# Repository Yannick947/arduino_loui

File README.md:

This repo can be used to play looping louie in different modes. Photocells are used to detect the chip count for each player. Automatic speech output is implemented and the game is stopped automatically when a player lost.

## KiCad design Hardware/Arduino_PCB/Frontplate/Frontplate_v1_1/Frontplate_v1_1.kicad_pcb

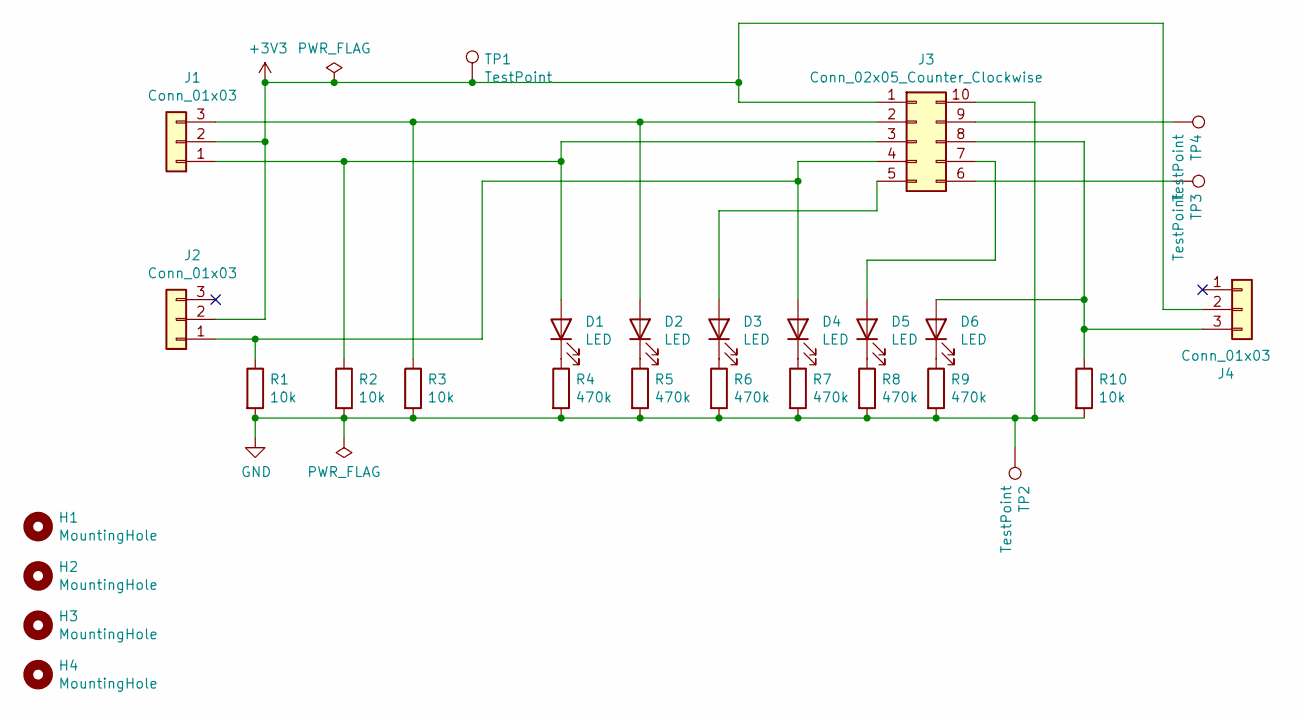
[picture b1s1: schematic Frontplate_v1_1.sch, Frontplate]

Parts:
D1, D2, D3, D4, D5, D6: LED; LED_D5.0mm
H1, H2, H3, H4: MountingHole; MountingHole_3.2mm_M3_DIN965_Pad
J1, J2, J4: Conn_01x03; PinHeader_1x03_P2.54mm_Vertical
J3: Conn_02x05_Counter_Clockwise; Muekra_10pol_Pfostenstecker
R1, R2, R3, R10: 10k; R_Axial_DIN0207_L6.3mm_D2.5mm_P10.16mm_Horizontal
R4, R5, R6, R7, R8, R9: 470k; R_Axial_DIN0207_L6.3mm_D2.5mm_P10.16mm_Horizontal
TP1, TP3, TP4: TestPoint; TestPoint_Pad_D2.0mm
TP2: TestPoint; TestPoint_Pad_2.0x2.0mm

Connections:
+3V3: J1.2, J2.2, J3.1, J4.2, TP1.1
GND: J3.10, R1.2, R2.2, R3.2, R4.2, R5.2, R6.2, R7.2, R8.2, R9.2, R10.2, TP2.1
unnamed: D1.1 (K), R4.1
unnamed: D1.2 (A), J1.1, J3.3, R2.1
unnamed: D2.1 (K), R5.1
unnamed: D2.2 (A), J1.3, J3.2, R3.1
unnamed: D3.1 (K), R6.1
unnamed: D3.2 (A), J3.5
unnamed: D4.1 (K), R7.1
unnamed: D4.2 (A), J2.1, J3.4, R1.1
unnamed: D5.1 (K), R8.1
unnamed: D5.2 (A), J3.7
unnamed: D6.1 (K), R9.1
unnamed: D6.2 (A), J3.8, J4.3, R10.1
unnamed: J3.6, TP3.1
unnamed: J3.9, TP4.1

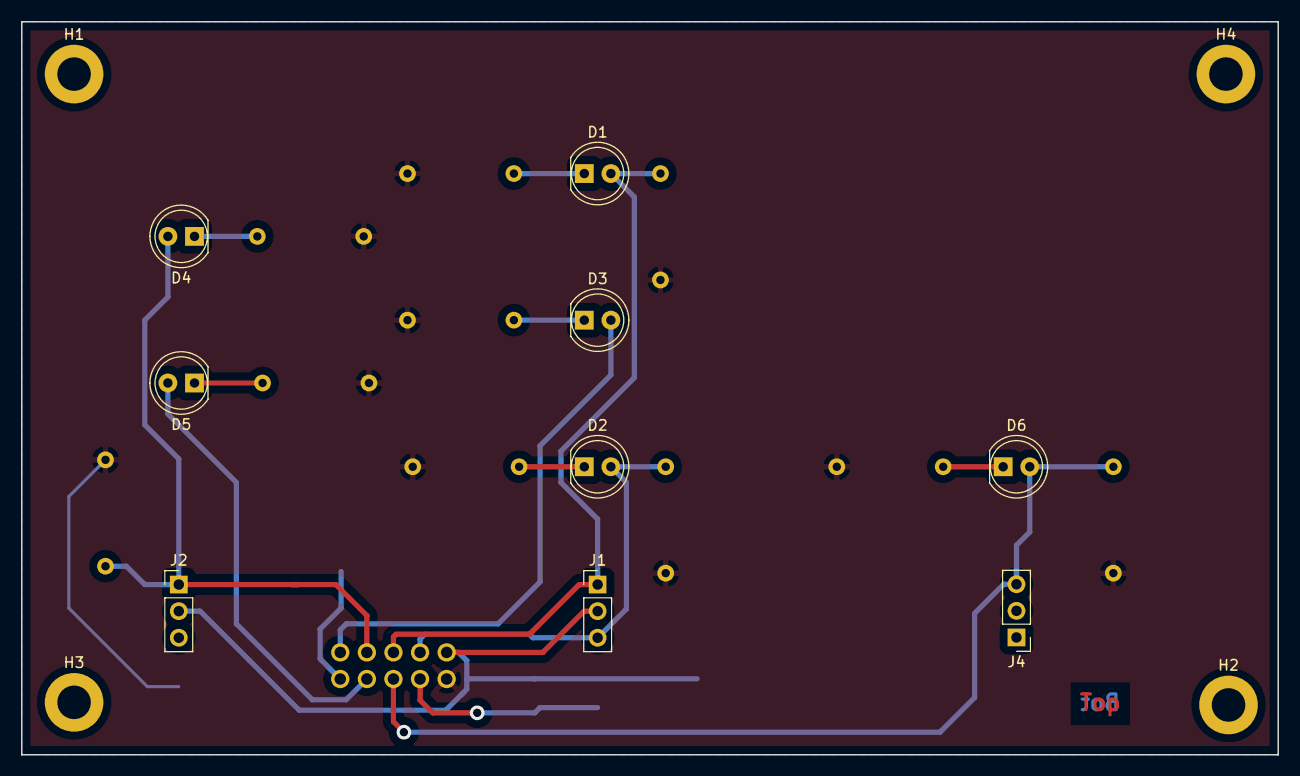
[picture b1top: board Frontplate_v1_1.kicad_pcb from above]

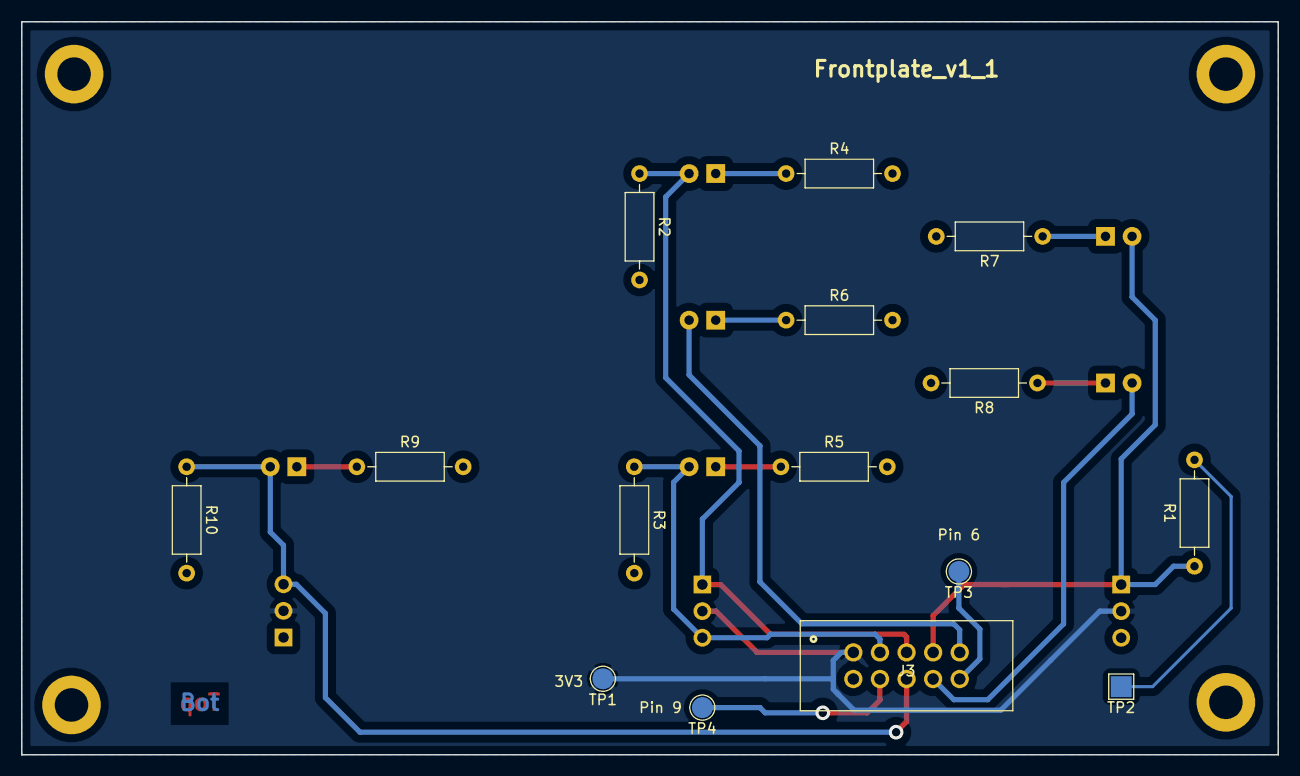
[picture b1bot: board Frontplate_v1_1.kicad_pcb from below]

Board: 2 copper layers, 120.0 x 70.0 mm, 28 parts (15 on the bottom side), 16 nets.

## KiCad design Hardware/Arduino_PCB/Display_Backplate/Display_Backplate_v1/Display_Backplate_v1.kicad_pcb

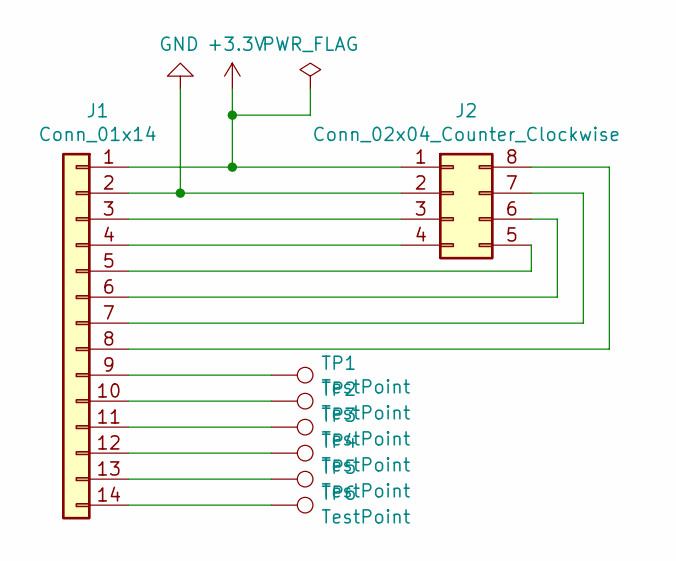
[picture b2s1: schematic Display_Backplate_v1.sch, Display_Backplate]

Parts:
J1: Conn_01x14; PinSocket_1x14_P2.54mm_Vertical
J2: Conn_02x04_Counter_Clockwise; Muekra_8pol_Pfostenstecker
TP1, TP2, TP3, TP4, TP5, TP6: TestPoint; TestPoint_Pad_D2.5mm

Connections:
+3V3: J1.1, J2.1
GND: J1.2, J2.2
unnamed: J1.3, J2.3
unnamed: J1.4, J2.4
unnamed: J1.5, J2.5
unnamed: J1.6, J2.6
unnamed: J1.7, J2.7
unnamed: J1.8, J2.8
unnamed: J1.9, TP1.1
unnamed: J1.10, TP2.1
unnamed: J1.11, TP3.1
unnamed: J1.12, TP4.1
unnamed: J1.13, TP5.1
unnamed: J1.14, TP6.1

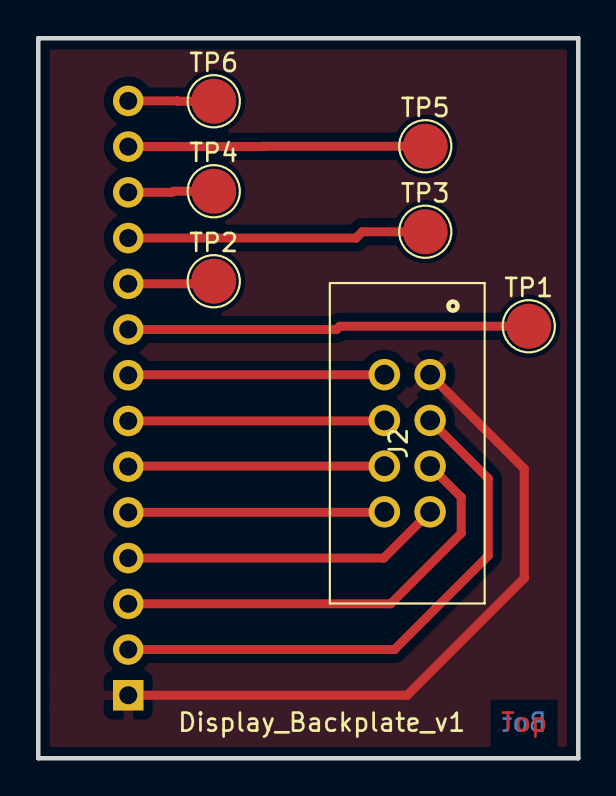
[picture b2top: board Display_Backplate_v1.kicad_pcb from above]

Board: 2 copper layers, 30.0 x 40.0 mm, 8 parts (1 on the bottom side), 14 nets.

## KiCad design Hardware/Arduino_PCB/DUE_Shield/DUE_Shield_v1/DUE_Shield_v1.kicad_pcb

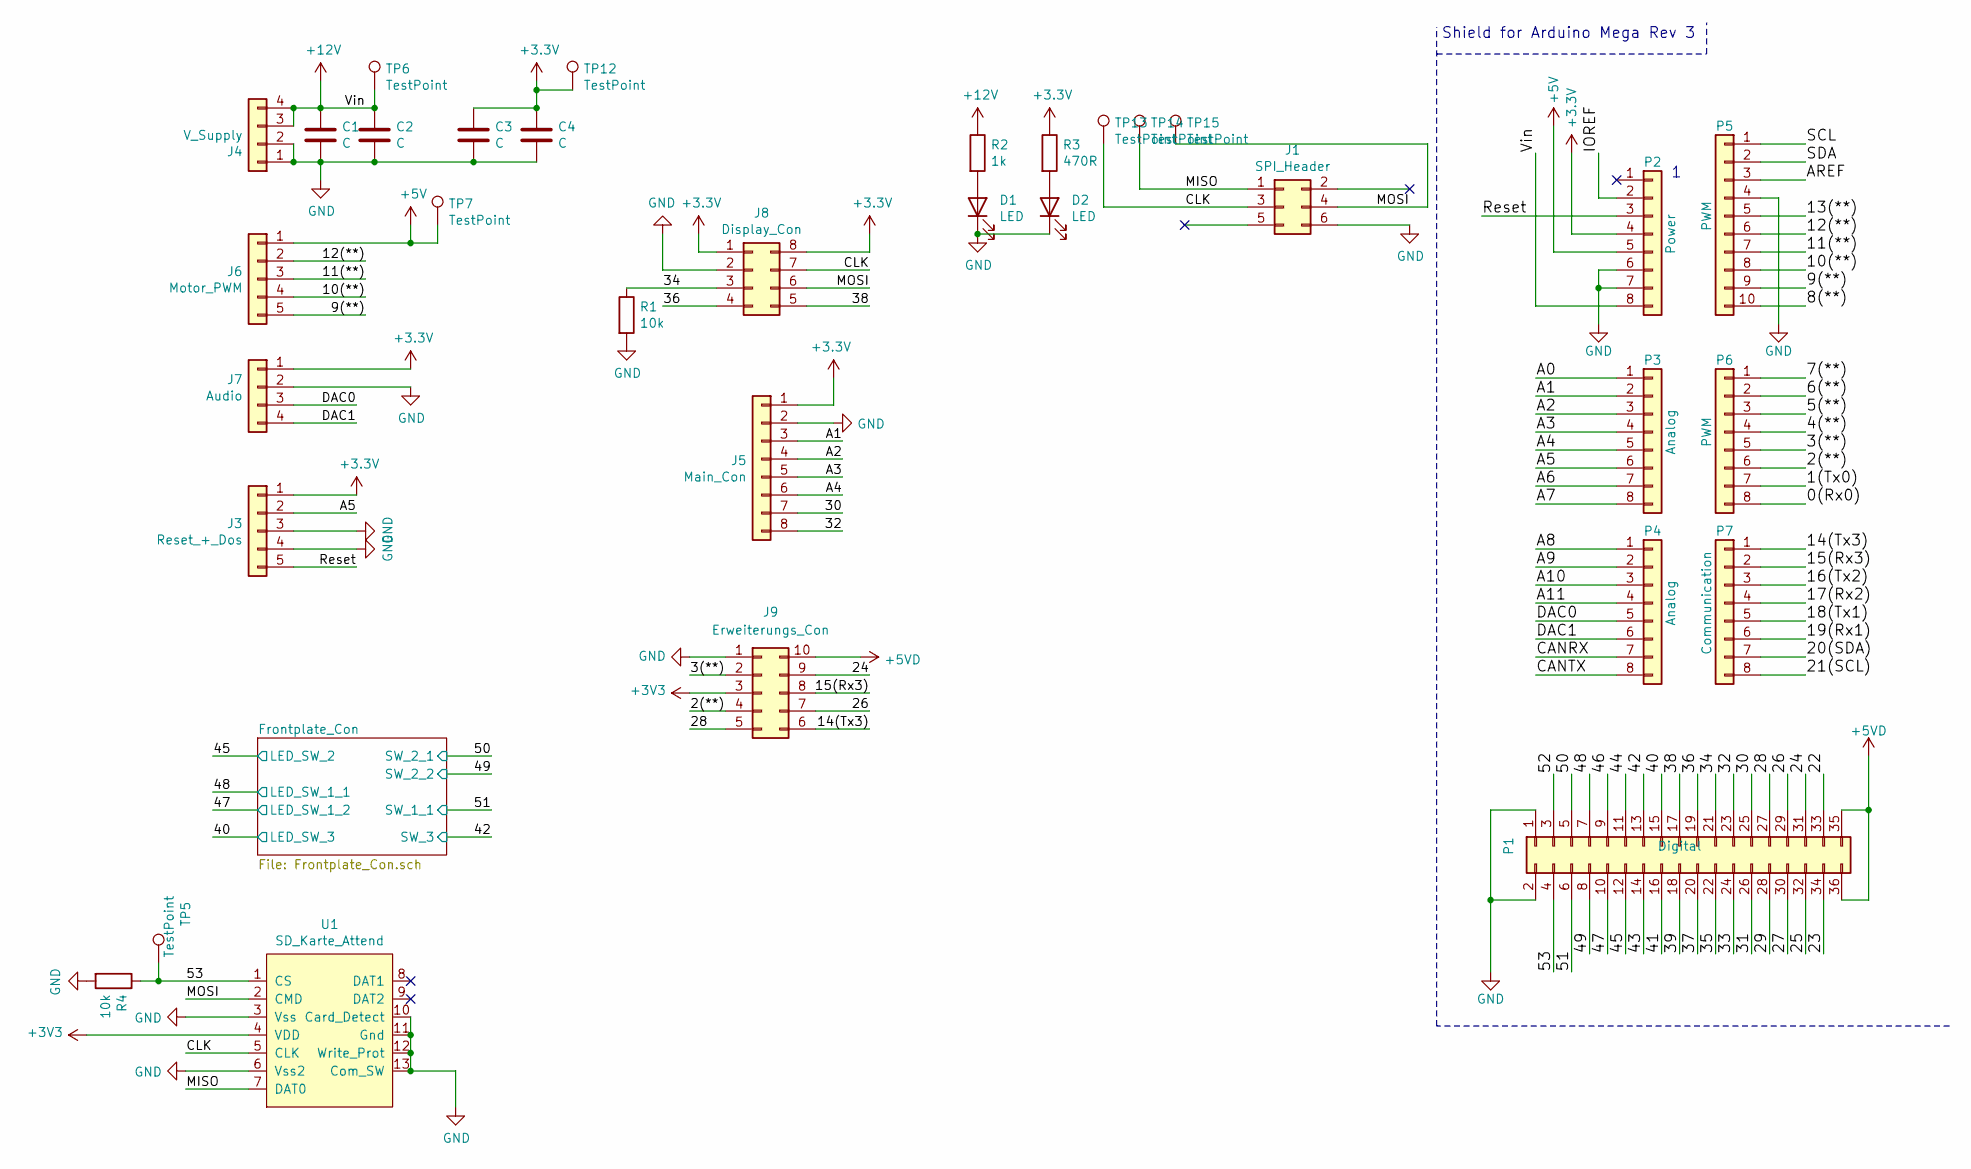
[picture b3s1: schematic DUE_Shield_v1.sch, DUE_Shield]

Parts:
C1, C2, C3, C4: C; C_0805_2012Metric
D1, D2: LED; LED_0805_2012Metric
J1: SPI_Header; PinSocket_2x03_P2.54mm_Vertical
J3: Reset_+_Dos; TerminalBlock_Phoenix_MPT-0,5-5-2.54_1x05_P2.54mm_Horizontal
J4: V_Supply; TerminalBlock_Phoenix_MPT-0,5-4-2.54_1x04_P2.54mm_Horizontal
J5: Main_Con; TerminalBlock_Phoenix_MPT-0,5-8-2.54_1x08_P2.54mm_Horizontal
J6: Motor_PWM; TerminalBlock_Phoenix_MPT-0,5-5-2.54_1x05_P2.54mm_Horizontal
J7: Audio; TerminalBlock_Phoenix_MPT-0,5-4-2.54_1x04_P2.54mm_Horizontal
J8: Display_Con; Muekra_8pol_Pfostenstecker
J9: Erweiterungs_Con; PinHeader_2x05_P2.54mm_Vertical
P1: Digital; PinHeader_2x18_P2.54mm_Vertical
P2: Power; PinHeader_1x08_P2.54mm_Vertical
P3, P4: Analog; PinHeader_1x08_P2.54mm_Vertical
P5: PWM; PinHeader_1x10_P2.54mm_Vertical
P6: PWM; PinHeader_1x08_P2.54mm_Vertical
P7: Communication; PinHeader_1x08_P2.54mm_Vertical
R1, R4: 10k; R_1206_3216Metric
R2: 1k; R_1206_3216Metric
R3: 470R; R_1206_3216Metric
TP5, TP6, TP7, TP12, TP13, TP14, TP15: TestPoint; TestPoint_Pad_D2.0mm
U1: SD_Karte_Attend; Attend_SD_104D_TCA0_R06

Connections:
+5V: J6.1, P2.5, TP7.1
+5VD: J9.10, P1.35, P1.36
+12V: C1.1, C2.1, J4.3, J4.4, P2.8, R2.1, TP6.1
/0(Rx0): P6.8
/1(Tx0): P6.7
/2(**): J9.4, P6.6
/3(**): J9.2, P6.5
/4(**): P6.4
/5(**): P6.3
/6(**): P6.2
/7(**): P6.1
/8(**): P5.10
/9(**): J6.5, P5.9
/10(**): J6.4, P5.8
/11(**): J6.3, P5.7
/12(**): J6.2, P5.6
/13(**): P5.5
/14(Tx3): J9.6, P7.1
/15(Rx3): J9.8, P7.2
/16(Tx2): P7.3
/17(Rx2): P7.4
/18(Tx1): P7.5
/19(Rx1): P7.6
/20(SDA): P7.7
/21(SCL): P7.8
/22: P1.33
/23: P1.34
/24: J9.9, P1.31
/25: P1.32
/26: J9.7, P1.29
/27: P1.30
/28: J9.5, P1.27
/29: P1.28
/30: J5.7, P1.25
/31: P1.26
/32: J5.8, P1.23
/33: P1.24
/34: J8.3, P1.21, R1.1
/35: P1.22
/36: J8.4, P1.19
/37: P1.20
/38: J8.5, P1.17
/39: P1.18
/40: P1.15; also elsewhere on the board
/41: P1.16
/42: P1.13; also elsewhere on the board
/43: P1.14
/44: P1.11
/45: P1.12; also elsewhere on the board
/46: P1.9
/47: P1.10; also elsewhere on the board
/48: P1.7; also elsewhere on the board
/49: P1.8; also elsewhere on the board
/50: P1.5; also elsewhere on the board
/51: P1.6; also elsewhere on the board
/52: P1.3
/53: P1.4, R4.1, TP5.1, U1.1 (CS)
/A0: P3.1
/A1: J5.3, P3.2
/A2: J5.4, P3.3
/A3: J5.5, P3.4
/A4: J5.6, P3.5
/A5: J3.2, P3.6
/A6: P3.7
/A7: P3.8
/A8: P4.1
/A9: P4.2
/A10: P4.3
/A11: P4.4
/AREF: P5.3
/CANRX: P4.7
/CANTX: P4.8
/CLK: J1.3, J8.7, TP13.1, U1.5 (CLK)
/DAC0: J7.3, P4.5
/DAC1: J7.4, P4.6
/IOREF: P2.2
/MISO: J1.1, TP14.1, U1.7 (DAT0)
/MOSI: J1.4, J8.6, TP15.1, U1.2 (CMD)
/Reset: J3.5, P2.3
/SCL: P5.1
/SDA: P5.2
GND: C1.2, C2.2, C3.2, C4.2, D1.1 (K), D2.1 (K), J1.6, J3.3, J3.4, J4.1, J4.2, J5.2, J7.2, J8.2, J9.1, P1.1, P1.2, P2.6, P2.7, P5.4, R1.2, R4.2, U1.3 (Vss), U1.6 (Vss2), U1.10 (Card_Detect), U1.11 (Gnd), U1.12 (Write_Prot), U1.13 (Com_SW); also elsewhere on the board
unnamed: D1.2 (A), R2.2
unnamed: D2.2 (A), R3.2

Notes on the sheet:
Shield for Arduino Mega Rev 3

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
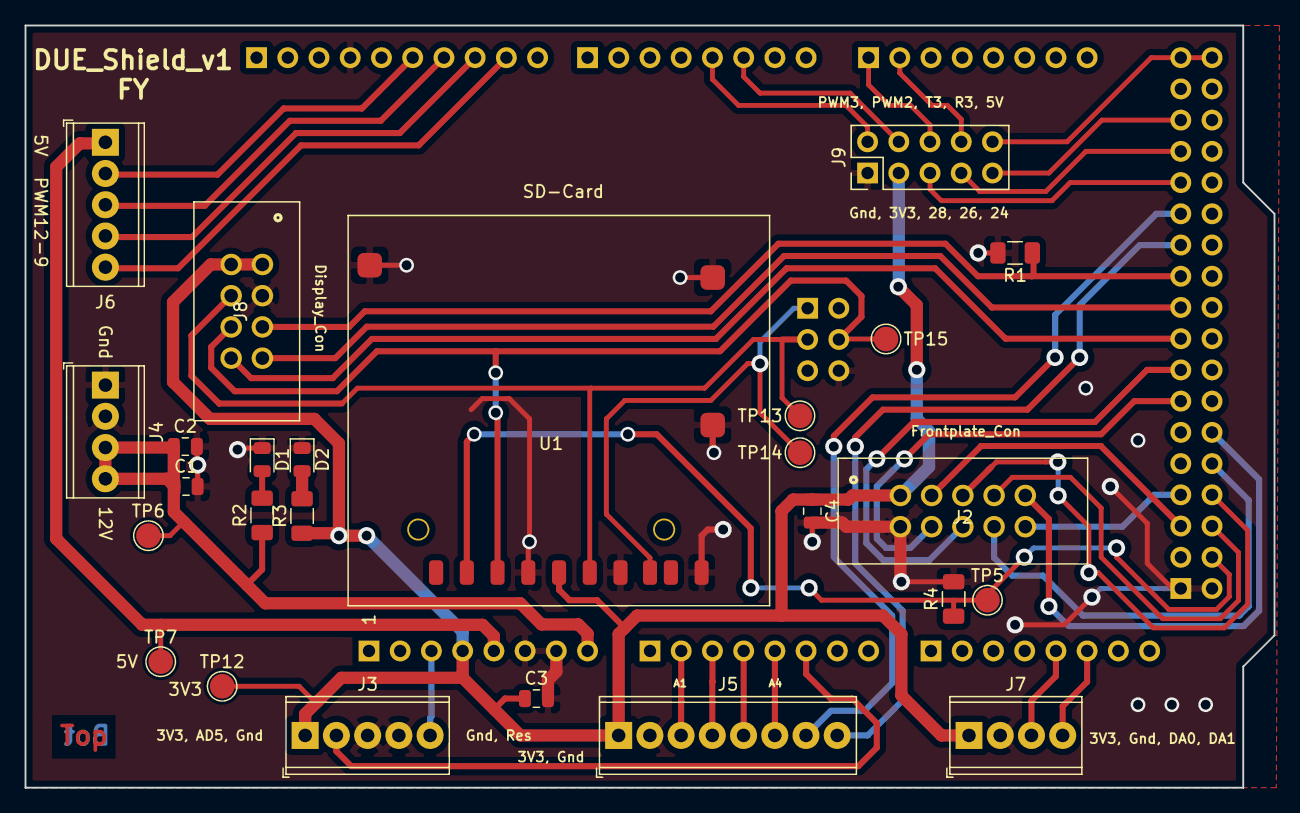
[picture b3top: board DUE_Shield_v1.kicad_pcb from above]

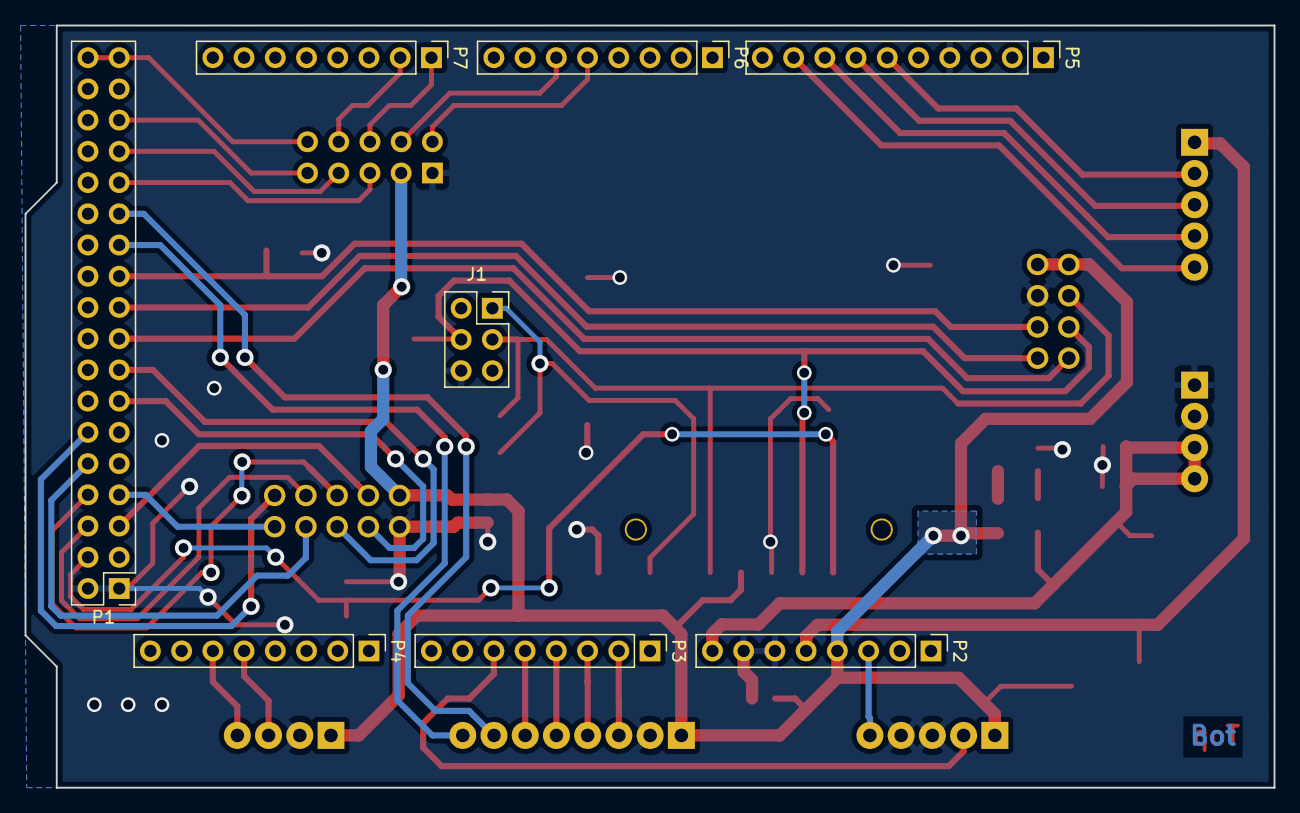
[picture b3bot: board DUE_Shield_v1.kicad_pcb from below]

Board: 2 copper layers, 101.6 x 62.0 mm, 34 parts (8 on the bottom side), 43 nets.

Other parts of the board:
J2: Conn_02x05_Counter_Clockwise; Muekra_10pol_Pfostenstecker

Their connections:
/40: J2.8; also elsewhere on the board
/42: J2.9; also elsewhere on the board
/45: J2.5; also elsewhere on the board
/47: J2.7; also elsewhere on the board
/48: J2.6; also elsewhere on the board
/49: J2.3; also elsewhere on the board
/50: J2.2; also elsewhere on the board
/51: J2.4; also elsewhere on the board
GND: J2.10; also elsewhere on the board

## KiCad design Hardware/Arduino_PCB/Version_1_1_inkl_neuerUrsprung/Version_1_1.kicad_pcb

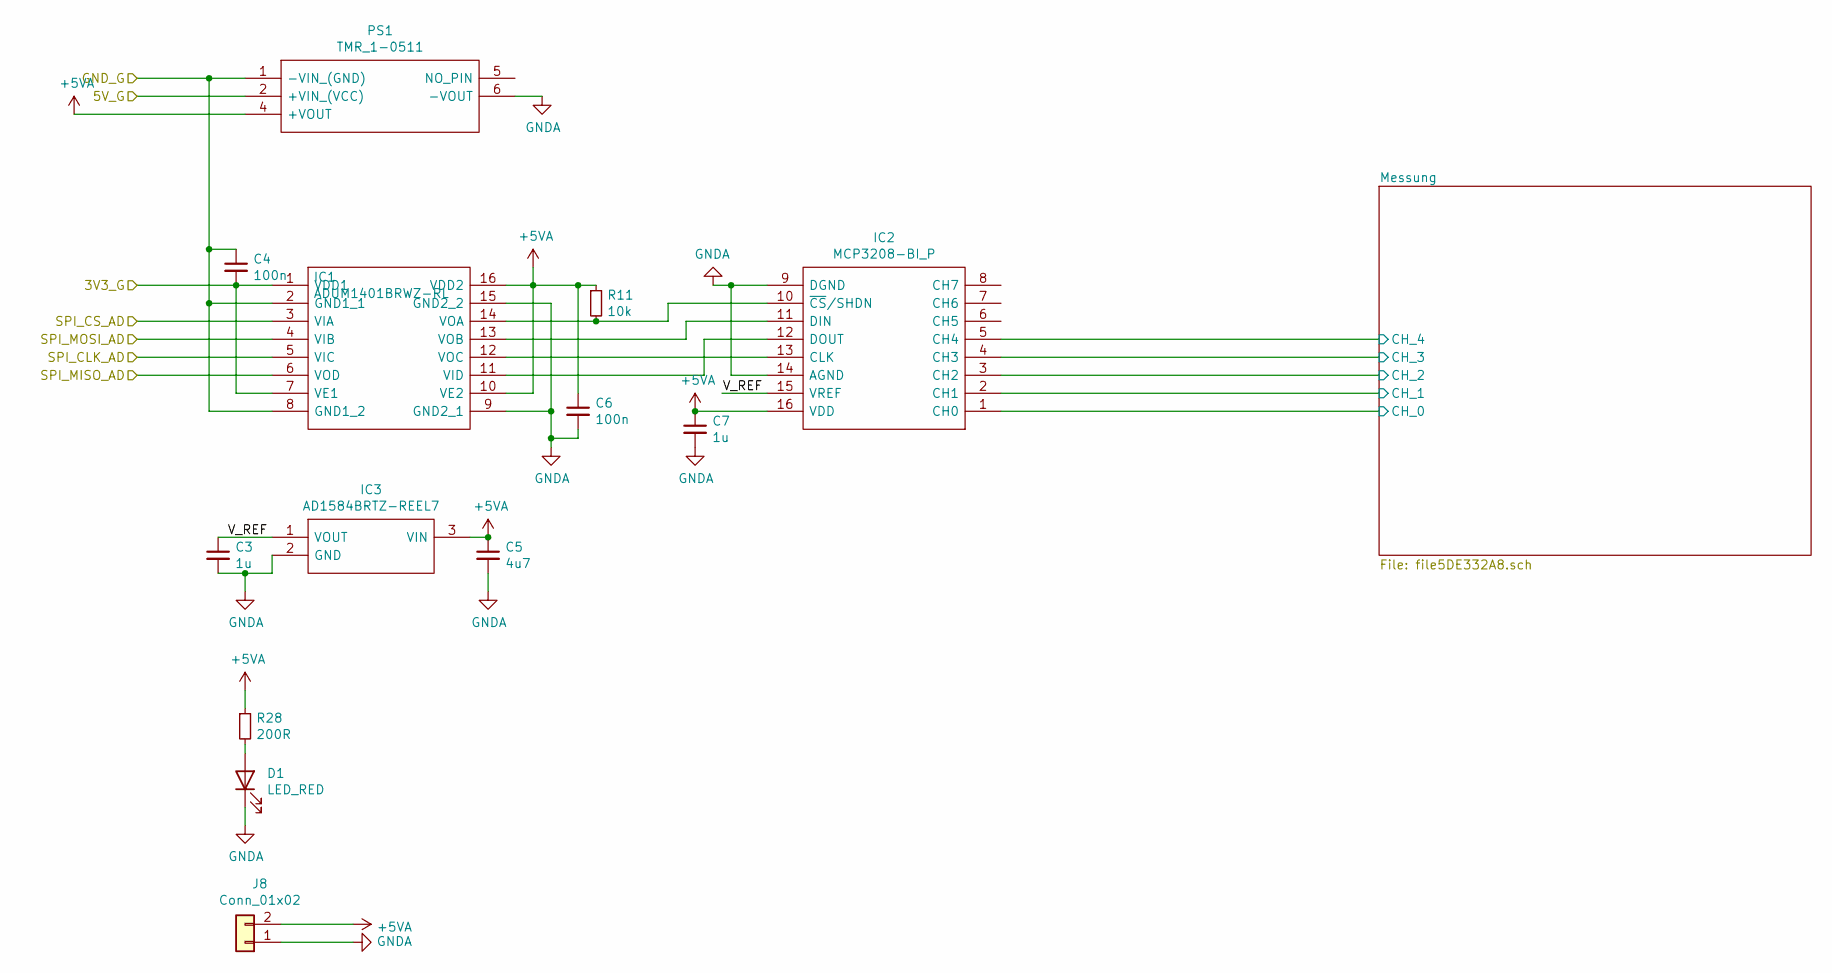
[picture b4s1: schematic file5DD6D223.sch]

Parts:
C3, C7: 1u; C_1206_3216Metric
C4, C6: 100n; C_1206_3216Metric
C5: 4u7; C_1206_3216Metric
D1: LED_RED; LED_1206_3216Metric
IC1: ADUM1401BRWZ-RL; SOIC127P1032X265-16N; Manufacturer_Part_Number ADUM1401BRWZ-RL; Mouser Part Number 584-ADUM1401BRWZ-R
IC2: MCP3208-BI_P; DIP781W56P254L1918H533Q16N; Manufacturer_Part_Number MCP3208-BI/P; Mouser Part Number 579-MCP3208-BI/P
IC3: AD1584BRTZ-REEL7; SOT95P264X112-3N; Manufacturer_Part_Number AD1584BRTZ-REEL7; Mouser Part Number 584-AD1584BRTZ-R7
J8: Conn_01x02; PinHeader_1x02_P2.54mm_Vertical
PS1: TMR_1-0511; TMR-1-1215; Manufacturer_Part_Number TMR 1-0511; Mouser Part Number 495-TMR-1-0511
R11: 10k; R_1206_3216Metric
R28: 200R; R_1206_3216Metric

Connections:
+3V3: C4.2, IC1.1 (VDD1), IC1.7 (VE1); also elsewhere on the board
+5V: PS1.2 (+VIN_(VCC)); also elsewhere on the board
+5VA: C5.1, C6.1, C7.1, IC1.10 (VE2), IC1.16 (VDD2), IC2.16 (VDD), IC3.3 (VIN), J8.2, PS1.4 (+VOUT), R11.1, R28.1; also elsewhere on the board
/Analog/Messung/Messung/CH_0: IC2.1 (CH0); also elsewhere on the board
/Analog/Messung/Messung/CH_1: IC2.2 (CH1); also elsewhere on the board
/Analog/Messung/Messung/CH_2: IC2.3 (CH2); also elsewhere on the board
/Analog/Messung/Messung/CH_3: IC2.4 (CH3); also elsewhere on the board
/Analog/Messung/Messung/CH_4: IC2.5 (CH4); also elsewhere on the board
/Analog/Messung/SPI_CLK_AD: IC1.5 (VIC); also elsewhere on the board
/Analog/Messung/SPI_CS_AD: IC1.3 (VIA); also elsewhere on the board
/Analog/Messung/SPI_MISO_AD: IC1.6 (VOD); also elsewhere on the board
/Analog/Messung/SPI_MOSI_AD: IC1.4 (VIB); also elsewhere on the board
/Analog/Messung/V_REF: C3.1, IC2.15 (VREF), IC3.1 (VOUT)
GND: C4.1, IC1.2 (GND1_1), IC1.8 (GND1_2), PS1.1 (-VIN_(GND)); also elsewhere on the board
GNDA: C3.2, C5.2, C6.2, C7.2, D1.1 (K), IC1.9 (GND2_1), IC1.15 (GND2_2), IC2.9 (DGND), IC2.14 (AGND), IC3.2 (GND), J8.1, PS1.6 (-VOUT); also elsewhere on the board
unnamed: D1.2 (A), R28.2
unnamed: IC1.11 (VID), IC2.12 (DOUT)
unnamed: IC1.12 (VOC), IC2.13 (CLK)
unnamed: IC1.13 (VOB), IC2.11 (DIN)
unnamed: IC1.14 (VOA), IC2.10 (~CS~/SHDN), R11.2

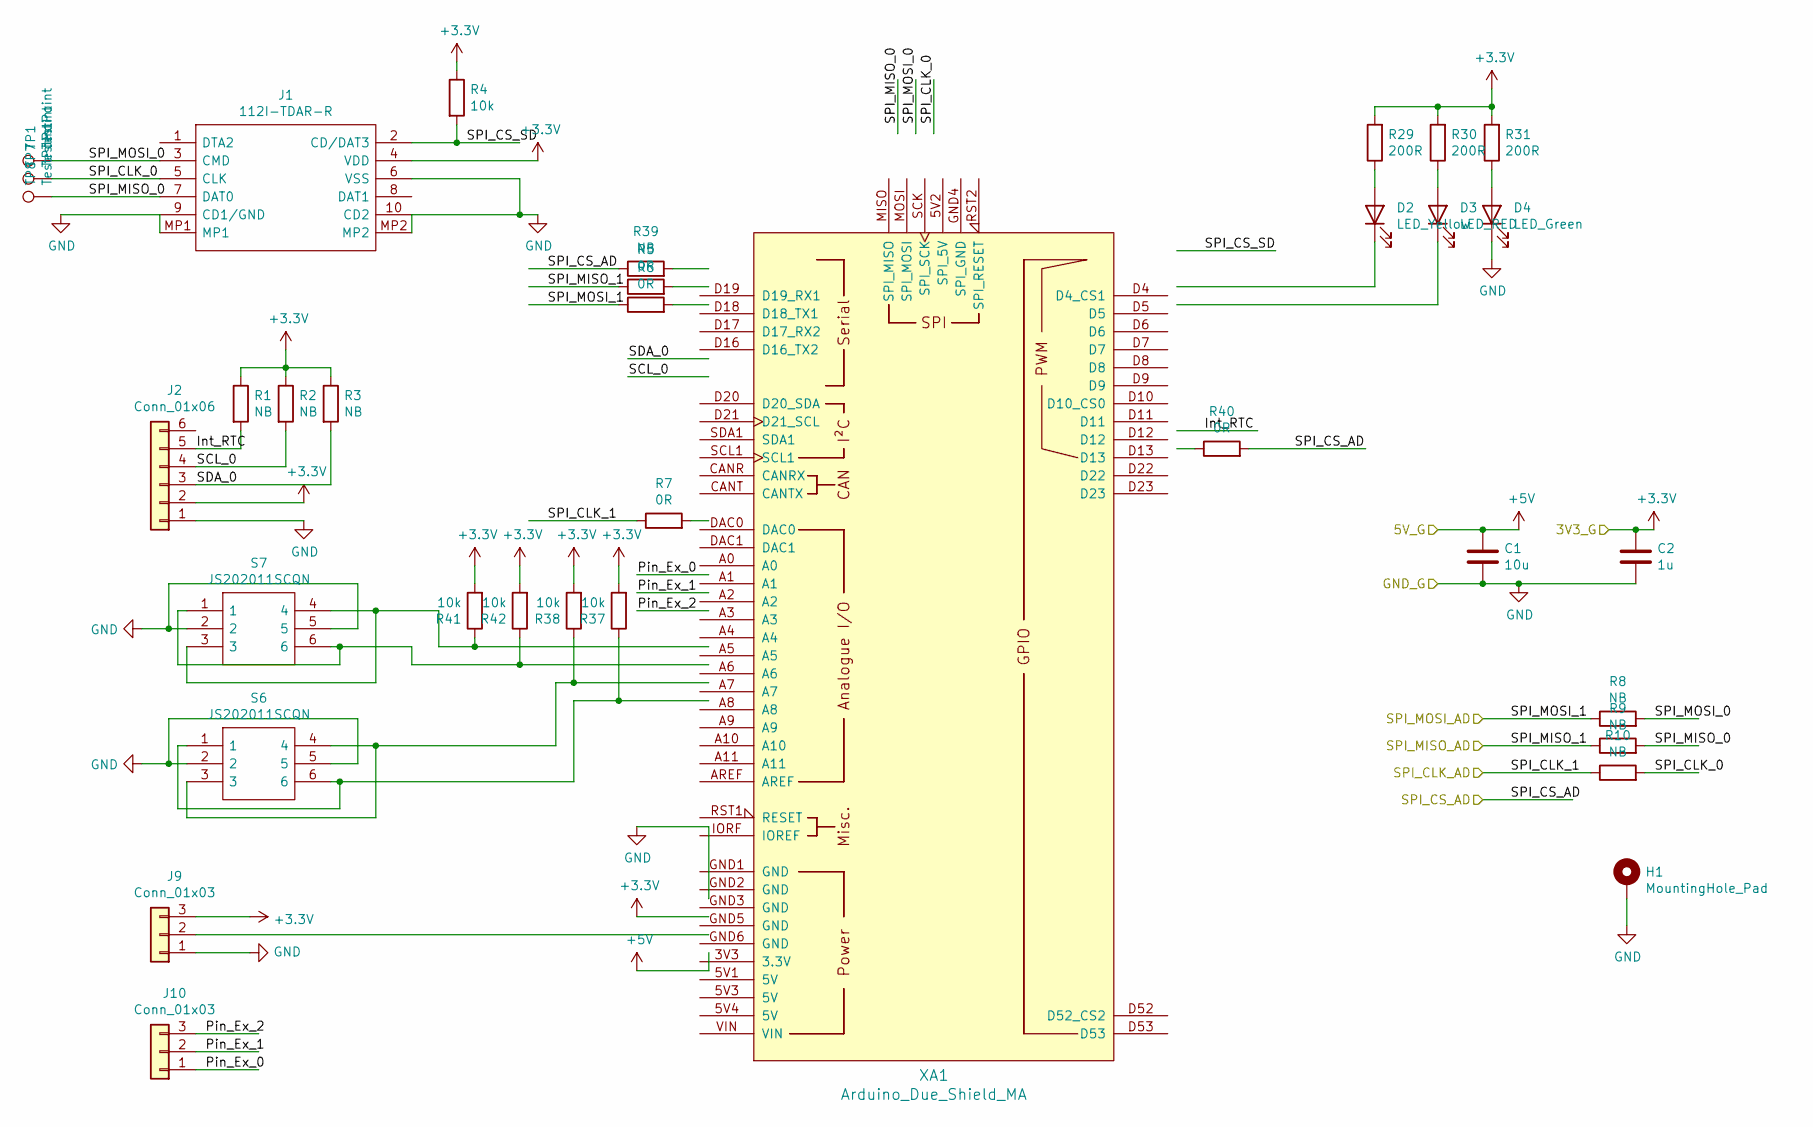
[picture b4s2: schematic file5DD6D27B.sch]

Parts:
C1: 10u; C_1206_3216Metric
C2: 1u; C_1206_3216Metric
D2: LED_Yellow; LED_1206_3216Metric
D3: LED_RED; LED_1206_3216Metric
D4: LED_Green; LED_1206_3216Metric
H1: MountingHole_Pad; MountingHole_4.3mm_M4_DIN965_Pad
J1: 112I-TDAR-R; 112ITDARR; Manufacturer_Part_Number 112I-TDAR-R
J2: Conn_01x06; PinHeader_1x06_P2.54mm_Vertical
J9, J10: Conn_01x03; PinHeader_1x03_P2.54mm_Vertical
R1, R2, R3, R8, R9, R10, R39: NB; R_1206_3216Metric
R4, R37, R38, R41, R42: 10k; R_1206_3216Metric
R5, R6, R7, R40: 0R; R_1206_3216Metric
R29, R30, R31: 200R; R_1206_3216Metric
S6, S7: JS202011SCQN; Manufacturer_Part_Number JS202011SCQN; Mouser Part Number 611-JS202011SCQN
TP1, TP7, TP8: TestPoint; TestPoint_Pad_D2.0mm
XA1: Arduino_Due_Shield_MA; Arduino_Due_Shield_MA_v2

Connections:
+3V3: C2.1, J1.4 (VDD), J2.2, J9.3, R1.1, R2.1, R3.1, R4.1, R29.2, R30.2, R31.2, R37.2, R38.2, R41.2, R42.2, XA1.3V3 (3.3V); also elsewhere on the board
+5V: C1.1, XA1.5V3 (5V), XA1.5V4 (5V); also elsewhere on the board
/Analog/Messung/SPI_CLK_AD: R7.1, R10.1; also elsewhere on the board
/Analog/Messung/SPI_CS_AD: R39.1, R40.2; also elsewhere on the board
/Analog/Messung/SPI_MISO_AD: R5.1, R9.1; also elsewhere on the board
/Analog/Messung/SPI_MOSI_AD: R6.1, R8.1; also elsewhere on the board
/Digital/Arduino/Int_RTC: J2.5, R1.2, XA1.D22
/Digital/Arduino/Pin_Ex_0: J10.1, XA1.A3
/Digital/Arduino/Pin_Ex_1: J10.2, XA1.A4
/Digital/Arduino/Pin_Ex_2: J10.3, XA1.A5
/Digital/Arduino/SCL_0: J2.4, R2.2, XA1.D21 (D21_SCL)
/Digital/Arduino/SDA_0: J2.3, R3.2, XA1.D20 (D20_SDA)
/Digital/Arduino/SPI_CLK_0: J1.5 (CLK), R10.2, TP7.1, XA1.SCK (SPI_SCK)
/Digital/Arduino/SPI_CS_SD: J1.2 (CD/DAT3), R4.2, XA1.D4 (D4_CS1)
/Digital/Arduino/SPI_MISO_0: J1.7 (DAT0), R9.2, TP8.1, XA1.MISO (SPI_MISO)
/Digital/Arduino/SPI_MOSI_0: J1.3 (CMD), R8.2, TP1.1, XA1.MOSI (SPI_MOSI)
GND: C1.2, C2.2, D4.1 (K), H1.1, J1.6 (VSS), J1.9 (CD1/GND), J1.10 (CD2), J1.MP1, J1.MP2, J2.1, J9.1, S6.2, S6.5, S7.2, S7.5, XA1.GND1 (GND), XA1.GND2 (GND), XA1.GND3 (GND), XA1.GND5 (GND), XA1.GND6 (GND); also elsewhere on the board
unnamed: D2.1 (K), XA1.D6
unnamed: D2.2 (A), R29.1
unnamed: D3.1 (K), XA1.D7
unnamed: D3.2 (A), R30.1
unnamed: D4.2 (A), R31.1
unnamed: J9.2, XA1.5V1 (5V)
unnamed: R5.2, XA1.D17 (D17_RX2)
unnamed: R6.2, XA1.D16 (D16_TX2)
unnamed: R7.2, XA1.A0
unnamed: R39.2, XA1.D18 (D18_TX1)
unnamed: R40.1, XA1.D23

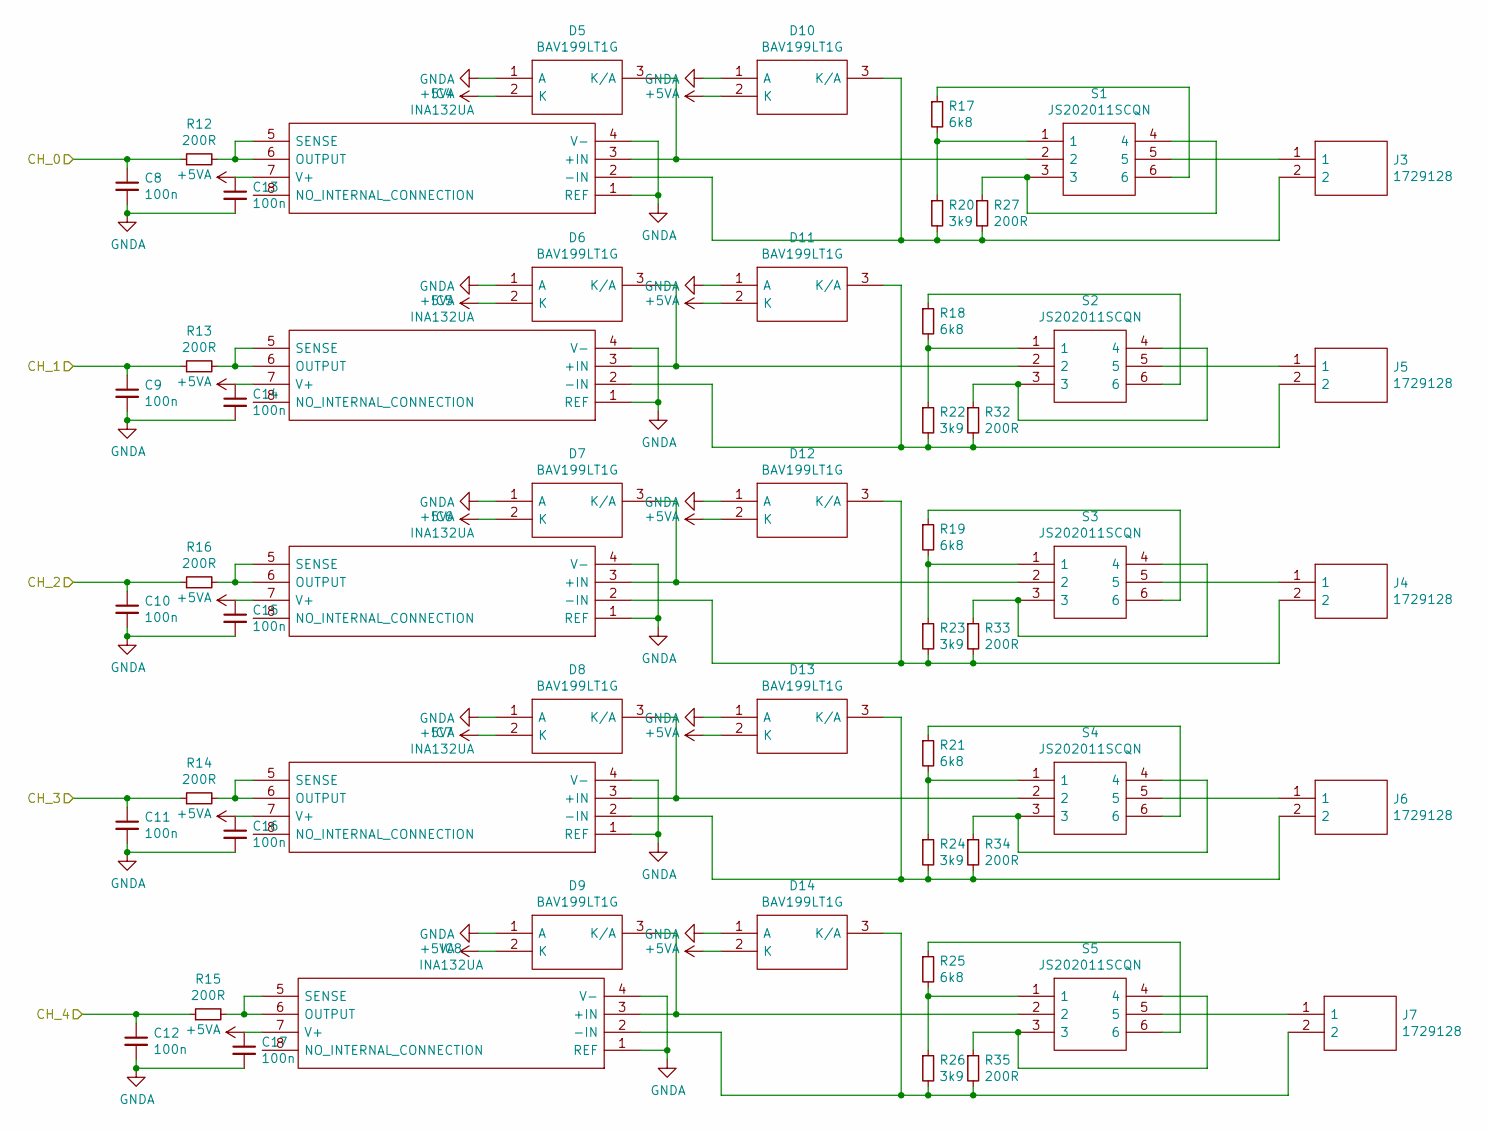
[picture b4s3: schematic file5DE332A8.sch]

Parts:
C8, C9, C10, C11, C12, C13, C14, C15, C16, C17: 100n; C_1206_3216Metric
D5, D6, D7, D8, D9, D10, D11, D12, D13, D14: BAV199LT1G; SOT96P237X111-3N; Manufacturer_Part_Number BAV199LT1G; Mouser Part Number 863-BAV199LT1G
IC4, IC5, IC6, IC7, IC8: INA132UA; SOIC127P600X175-8N; Manufacturer_Part_Number INA132UA; Mouser Part Number 595-INA132UA
J3, J4, J5, J6, J7: 1729128; HDRV2W110P0X508_1X2_1016X810X1000P; Manufacturer_Part_Number 1729128; Mouser Part Number 651-1729128
R12, R13, R14, R15, R16, R27, R32, R33, R34, R35: 200R; R_1206_3216Metric
R17, R18, R19, R21, R25: 6k8; R_1206_3216Metric
R20, R22, R23, R24, R26: 3k9; R_1206_3216Metric
S1, S2, S3, S4, S5: JS202011SCQN; Manufacturer_Part_Number JS202011SCQN; Mouser Part Number 611-JS202011SCQN

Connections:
+5VA: C13.1, C14.1, C15.1, C16.1, C17.1, D5.2 (K), D6.2 (K), D7.2 (K), D8.2 (K), D9.2 (K), D10.2 (K), D11.2 (K), D12.2 (K), D13.2 (K), D14.2 (K), IC4.7 (V+), IC5.7 (V+), IC6.7 (V+), IC7.7 (V+), IC8.7 (V+); also elsewhere on the board
/Analog/Messung/Messung/CH_0: C8.1, R12.1; also elsewhere on the board
/Analog/Messung/Messung/CH_1: C9.1, R13.1; also elsewhere on the board
/Analog/Messung/Messung/CH_2: C10.1, R16.1; also elsewhere on the board
/Analog/Messung/Messung/CH_3: C11.1, R14.1; also elsewhere on the board
/Analog/Messung/Messung/CH_4: C12.1, R15.1; also elsewhere on the board
GNDA: C8.2, C9.2, C10.2, C11.2, C12.2, C13.2, C14.2, C15.2, C16.2, C17.2, D5.1 (A), D6.1 (A), D7.1 (A), D8.1 (A), D9.1 (A), D10.1 (A), D11.1 (A), D12.1 (A), D13.1 (A), D14.1 (A), IC4.1 (REF), IC4.4 (V-), IC5.1 (REF), IC5.4 (V-), IC6.1 (REF), IC6.4 (V-), IC7.1 (REF), IC7.4 (V-), IC8.1 (REF), IC8.4 (V-); also elsewhere on the board
unnamed: D5.3 (K/A), IC4.3 (+IN), S1.2
unnamed: D6.3 (K/A), IC5.3 (+IN), S2.2
unnamed: D7.3 (K/A), IC6.3 (+IN), S3.2
unnamed: D8.3 (K/A), IC7.3 (+IN), S4.2
unnamed: D9.3 (K/A), IC8.3 (+IN), S5.2
unnamed: D10.3 (K/A), IC4.2 (-IN), J3.2, R20.2, R27.2
unnamed: D11.3 (K/A), IC5.2 (-IN), J5.2, R22.2, R32.2
unnamed: D12.3 (K/A), IC6.2 (-IN), J4.2, R23.2, R33.2
unnamed: D13.3 (K/A), IC7.2 (-IN), J6.2, R24.2, R34.2
unnamed: D14.3 (K/A), IC8.2 (-IN), J7.2, R26.2, R35.2
unnamed: IC4.5 (SENSE), IC4.6 (OUTPUT), R12.2
unnamed: IC5.5 (SENSE), IC5.6 (OUTPUT), R13.2
unnamed: IC6.5 (SENSE), IC6.6 (OUTPUT), R16.2
unnamed: IC7.5 (SENSE), IC7.6 (OUTPUT), R14.2
unnamed: IC8.5 (SENSE), IC8.6 (OUTPUT), R15.2
unnamed: J3.1, S1.5
unnamed: J4.1, S3.5
unnamed: J5.1, S2.5
unnamed: J6.1, S4.5
unnamed: J7.1, S5.5
unnamed: R17.1, S1.6
unnamed: R17.2, R20.1, S1.1
unnamed: R18.1, S2.6
unnamed: R18.2, R22.1, S2.1
unnamed: R19.1, S3.6
unnamed: R19.2, R23.1, S3.1
unnamed: R21.1, S4.6
unnamed: R21.2, R24.1, S4.1
unnamed: R25.1, S5.6
unnamed: R25.2, R26.1, S5.1
unnamed: R27.1, S1.3, S1.4
unnamed: R32.1, S2.3, S2.4
unnamed: R33.1, S3.3, S3.4
unnamed: R34.1, S4.3, S4.4
unnamed: R35.1, S5.3, S5.4

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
